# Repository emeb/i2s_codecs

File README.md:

# i2s_codecs

## Abstract
This repository is a collection of hardware and software for evaluating I2S codecs
for use in digital audio projects. I've been using codecs for personal and commercial
applications for more than a decade now and I've seen a lot of them come and go. Recently
several of my go-to codecs went EOL and I had to dive back into the distributors sites to
find a new one to use for some upcoming projects. The first one I tried had some very
odd behavior so I picked a few more, built some breakout boards and a little I2S signal
generator for comparing them all on even footing. The designs here are the result of
that effort.

## Hardware
There are two subdirectories here with KiCAD hardware designs that I used:
* `codec_pmods` - these are simple breakout boards for a number of different codecs,
some of which are currently available, some are obsolete. They are small 2-layer
boards intended to provide minimal support for the codec devices with little to
no attention to audio signal conditioning. The I2S interface is through a standard
12-pin (8 signals + 4 power & ground) PMOD connector that also provides 3 GPIO pins
that support I2C or bitbang configuration protocols that some codecs require for
startup.
* `rp2040_i2s_tester` - this is a KiCAD design for an RP2040 MCU that can drive the
12-pin PMOD with appropriate I2S, I2C or bitbang as well as 3.3V power. It uses a
USB-C connector for power and bootloading but also provides a Qwiic I2C connector,
a blinky LED and a user-defined button for mode selection.

## Software
The directory `Firmware` contains a Raspberry Pi SDK project with basic firmware
for the `rp2040_i2s_tester` board.

## Going Further
This is bare-bones stuff but can support more complex stuff in the future. I may
investigate USB Audio class drivers for interfacing the codecs to a host. There are
also a wide range of other codecs I may add to the list of breakouts. Time will tell.

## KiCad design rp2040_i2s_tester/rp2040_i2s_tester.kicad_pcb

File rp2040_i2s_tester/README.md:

# RP2040_I2S_Tester
I2S Signal Generator for testing CODECs

## Abstract
This directory contains a KiCAD design for an RP2040-based I2S signal generator
that can drive the CODEC PMODs described elsewhere in this repository.

## Firmware
The RP2040 firmware for this design can be found elsewhere in this repository.

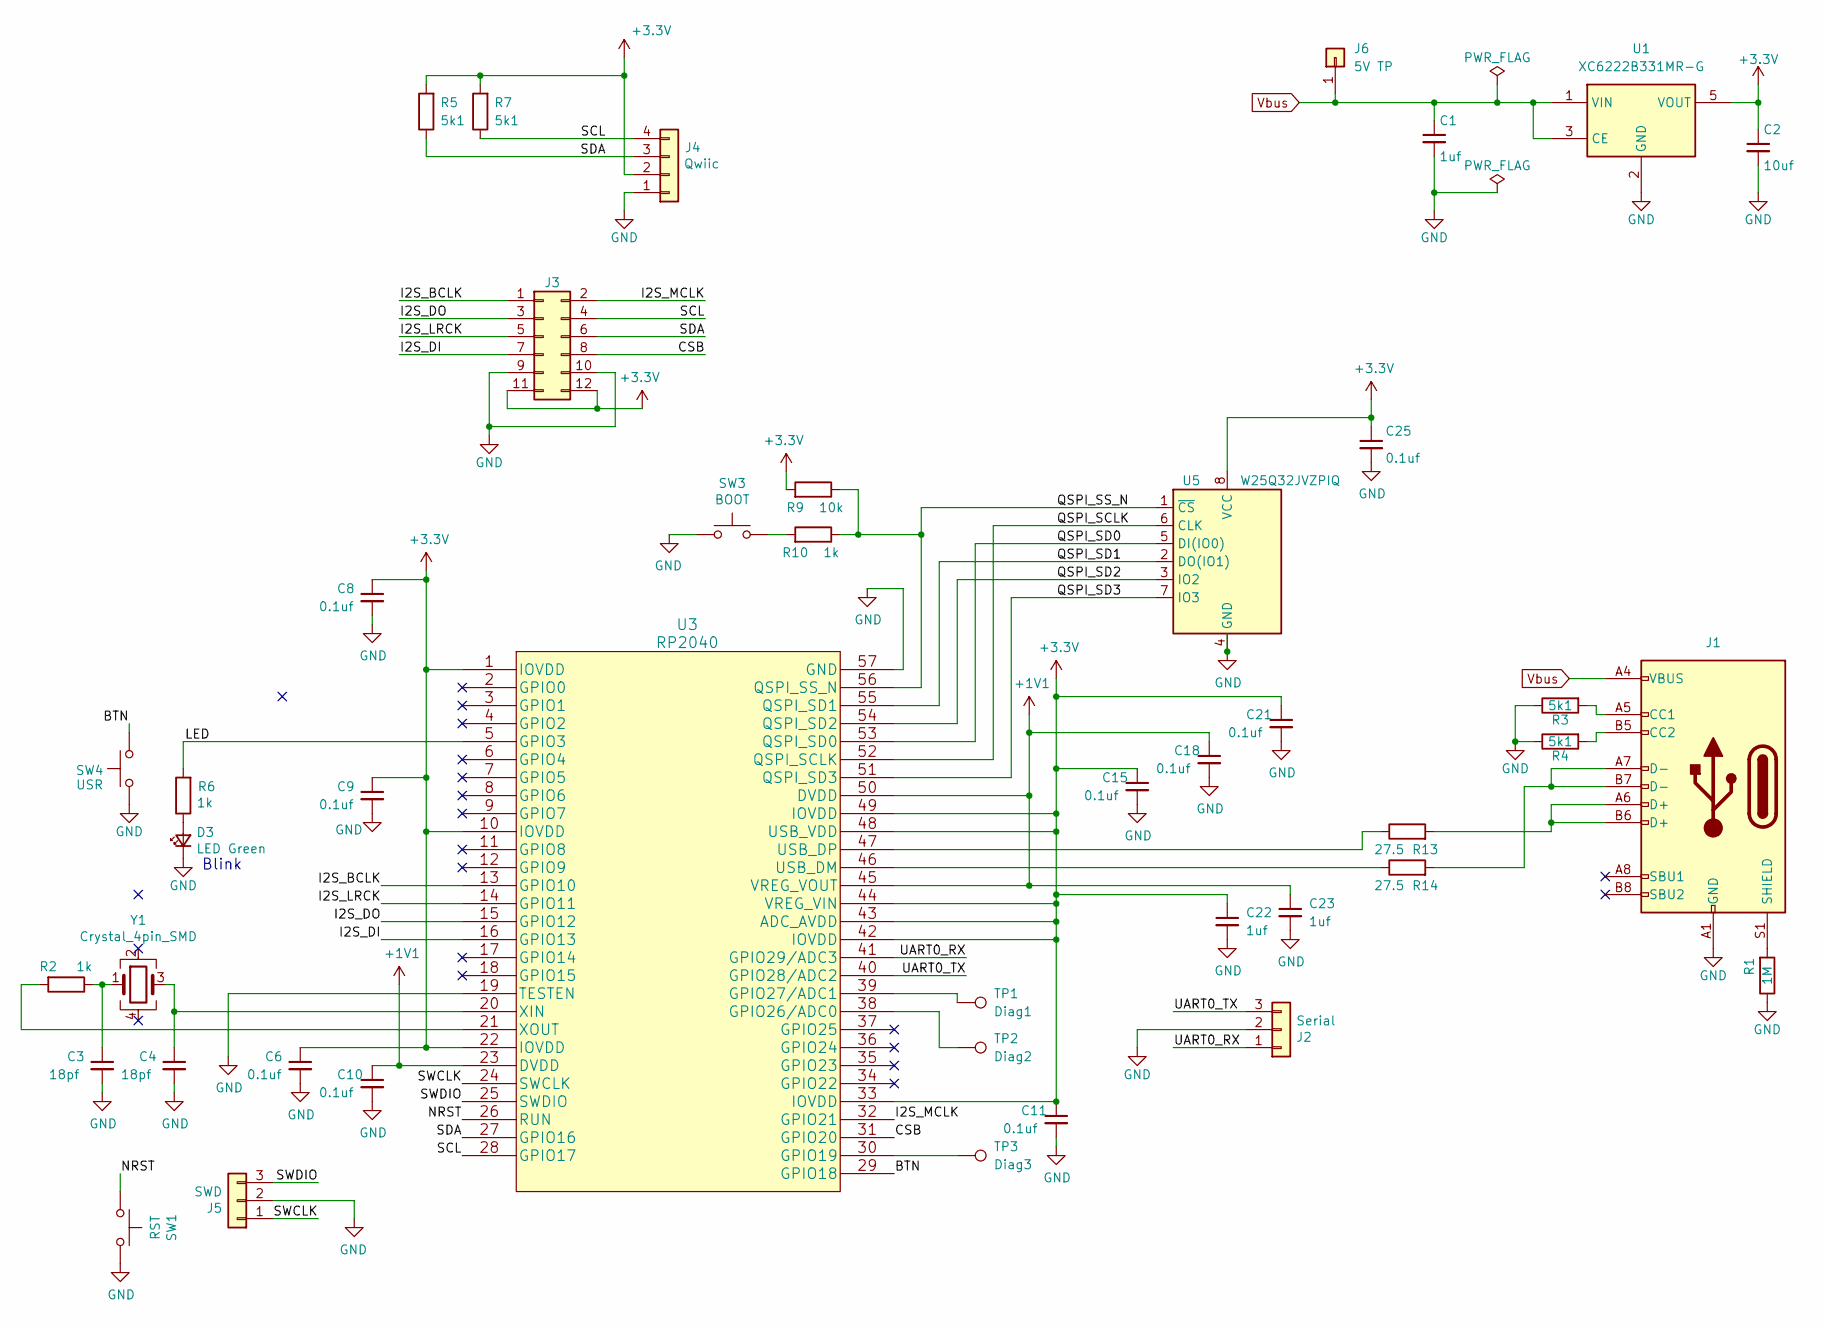
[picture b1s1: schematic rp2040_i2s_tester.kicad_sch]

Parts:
C1, C22, C23: 1uf; C_0402_1005Metric
C2: 10uf; C_0805_2012Metric
C3, C4: 18pf; C_0402_1005Metric
C6, C8, C9, C10, C11, C15, C18, C21, C25: 0.1uf; C_0402_1005Metric
D3: LED Green; LED_0603_1608Metric
J1: USB_C_Receptacle_USB2.0; USB_C_Receptacle_HRO_TYPE-C-31-M-12
J2: Serial; JST_SH_SM03B-SRSS-TB_1x03-1MP_P1.00mm_Horizontal
J3: CONN_02X06; PinSocket_2x06_P2.54mm_Vertical
J4: Qwiic; JST_SH_SM04B-SRSS-TB_04x1.00mm_Angled
J5: SWD; JST_SH_SM03B-SRSS-TB_1x03-1MP_P1.00mm_Horizontal
J6: 5V TP; PinHeader_1x01_P2.54mm_Vertical
R1: 1M; R_0402_1005Metric
R2, R6, R10: 1k; R_0402_1005Metric
R3, R4, R5, R7: 5k1; R_0402_1005Metric
R9: 10k; R_0402_1005Metric
R13, R14: 27.5; R_0402_1005Metric
SW1: RST; SW_Push_1P1T_NO_CK_KMR2
SW3: BOOT; SW_Push_1P1T_NO_CK_KMR2
SW4: USR; SW_Push_1P1T_NO_CK_KMR2
TP1: Diag1; TestPoint_Pad_D1.0mm
TP2: Diag2; TestPoint_Pad_D1.0mm
TP3: Diag3; TestPoint_Pad_D1.0mm
U1: XC6222B331MR-G; SOT-23-5
U3: RP2040
U5: W25Q32JVZPIQ; WSON-8-1EP_6x5mm_P1.27mm_EP3.4x4.3mm
Y1: Crystal_4pin_SMD; Crystal_SMD_3225-4Pin_3.2x2.5mm

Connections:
+1V1: C10.1, C18.1, C23.1, U3.23 (DVDD), U3.45 (VREG_VOUT), U3.50 (DVDD)
+3.3V: C2.1, C6.1, C8.1, C9.1, C11.1, C15.1, C21.1, C22.1, C25.1, J3.11, J3.12, J4.2, R5.2, R7.2, R9.2, U1.5 (VOUT), U3.1 (IOVDD), U3.10 (IOVDD), U3.22 (IOVDD), U3.33 (IOVDD), U3.42 (IOVDD), U3.43 (ADC_AVDD), U3.44 (VREG_VIN), U3.48 (USB_VDD), U3.49 (IOVDD), U5.8 (VCC)
/BTN: SW4.2, U3.29 (GPIO18)
/CSB: J3.8, U3.31 (GPIO20)
/I2S_BCLK: J3.1, U3.13 (GPIO10)
/I2S_DI: J3.7, U3.16 (GPIO13)
/I2S_DO: J3.3, U3.15 (GPIO12)
/I2S_LRCK: J3.5, U3.14 (GPIO11)
/I2S_MCLK: J3.2, U3.32 (GPIO21)
/LED: R6.2, U3.5 (GPIO3)
/NRST: SW1.1, U3.26 (RUN)
/QSPI_SCLK: U3.52 (QSPI_SCLK), U5.6 (CLK)
/QSPI_SD0: U3.53 (QSPI_SD0), U5.5 (DI(IO0))
/QSPI_SD1: U3.55 (QSPI_SD1), U5.2 (DO(IO1))
/QSPI_SD2: U3.54 (QSPI_SD2), U5.3 (IO2)
/QSPI_SD3: U3.51 (QSPI_SD3), U5.7 (IO3)
/QSPI_SS_N: R9.1, R10.1, U3.56 (QSPI_SS_N), U5.1 (~CS)
/SCL: J3.4, J4.4, R7.1, U3.28 (GPIO17)
/SDA: J3.6, J4.3, R5.1, U3.27 (GPIO16)
/SWCLK: J5.1, U3.24 (SWCLK)
/SWDIO: J5.3, U3.25 (SWDIO)
/UART0_RX: J2.1, U3.41 (GPIO29/ADC3)
/UART0_TX: J2.3, U3.40 (GPIO28/ADC2)
GND: C1.2, C2.2, C3.2, C4.2, C6.2, C8.2, C9.2, C10.2, C11.2, C15.2, C18.2, C21.2, C22.2, C23.2, C25.2, D3.1 (K), J1.A1 (GND), J1.A12 (GND), J1.B1 (GND), J1.B12 (GND), J2.2, J3.9, J3.10, J4.1, J5.2, R1.1, R3.1, R4.1, SW1.2, SW3.2, SW4.1, U1.2 (GND), U3.19 (TESTEN), U3.57 (GND), U5.4 (GND)
unnamed: C3.1, R2.1, Y1.1
unnamed: D3.2 (A), R6.1
unnamed: J1.A5 (CC1), R3.2
unnamed: J1.B5 (CC2), R4.2
unnamed: J1.A6 (D+), J1.B6 (D+), R13.2
unnamed: J1.A7 (D-), J1.B7 (D-), R14.2
unnamed: J1.S1 (SHIELD), R1.2
unnamed: R10.2, SW3.1
unnamed: TP3.1, U3.30 (GPIO19)
unnamed: TP2.1, U3.38 (GPIO26/ADC0)
unnamed: TP1.1, U3.39 (GPIO27/ADC1)
unnamed: R14.1, U3.46 (USB_DM)
unnamed: R13.1, U3.47 (USB_DP)
unnamed: C4.1, U3.20 (XIN), Y1.3
unnamed: R2.2, U3.21 (XOUT)
Vbus: C1.1, J1.A4 (VBUS), J1.A9 (VBUS), J1.B4 (VBUS), J1.B9 (VBUS), J6.1, U1.1 (VIN), U1.3 (CE)

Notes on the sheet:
Blink

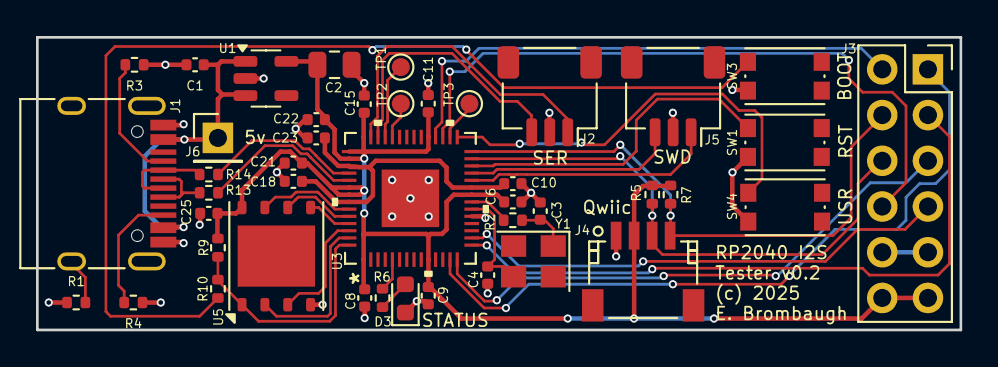
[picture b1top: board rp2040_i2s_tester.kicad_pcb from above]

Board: 2 copper layers, 51.3 x 16.3 mm, 43 parts (0 on the bottom side), 40 nets.

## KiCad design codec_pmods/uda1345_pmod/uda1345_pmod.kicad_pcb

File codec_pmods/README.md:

# CODEC PMODS
This directory contains KiCAD designs for various CODEC PMOD breakout boards. The
following boards have been built and tested:
* WM8731 - this is an earlier design found in an [older repository](https://github.com/emeb/Old_Website/tree/main/synth/codec_pmod).
It's a venerable codec that's been used in a lot of computers and media players as well as
add-on boards for the Raspberry Pi but now it's obsolete.
* TLV320AIC3101 - this is a currently available (as of 2025) codec that has some interesting
peculiarities that may make it unsuitable for some applications.
* NAU88C22 - this is an inexpensive codec with a lot of interesting features that seems to
perform reasonably well.
* SGTL5000 - this one has been around for a while and is still available. It's notable for its
small size.
* UDA1345 - This is a long obsolete part that I included just because I had a few in my
parts inventory that I'd never tried out. It's idiosyncratic.

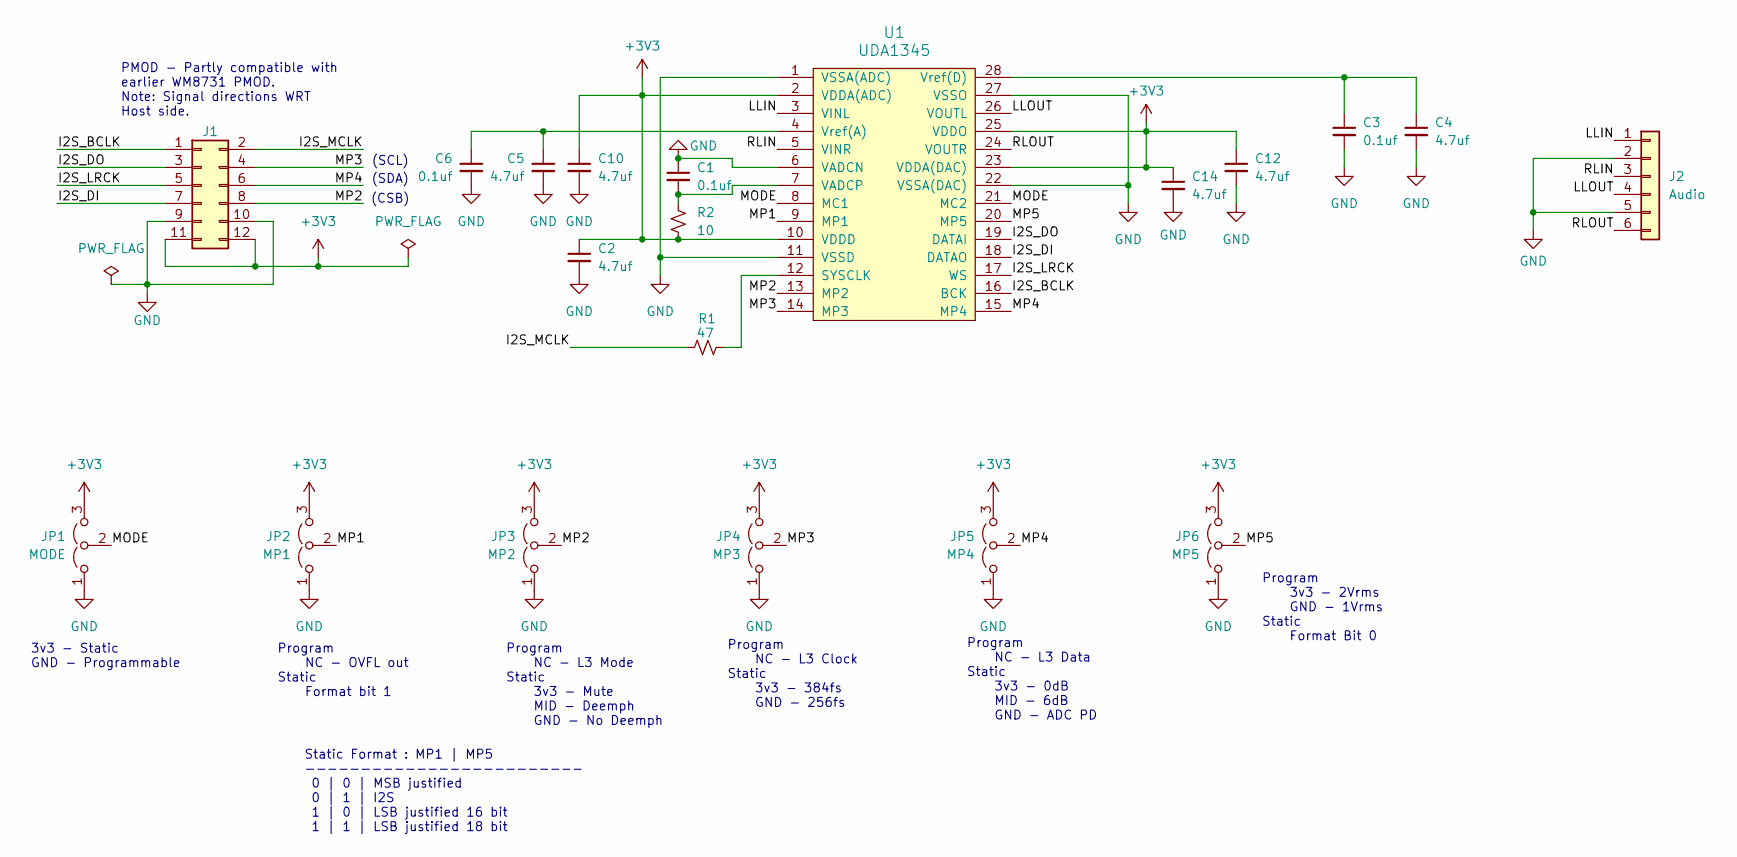
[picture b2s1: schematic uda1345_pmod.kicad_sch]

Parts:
C1, C3, C6: 0.1uf; C_0402_1005Metric
C2, C4, C5, C10, C12, C14: 4.7uf; C_0402_1005Metric
J1: CONN_02X06; PinHeader_2x06_P2.54mm_Vertical
J2: Audio; PinHeader_1x06_P2.54mm_Vertical
JP1: MODE; SolderJumper-3_P1.3mm_Open_RoundedPad1.0x1.5mm
JP2: MP1; SolderJumper-3_P1.3mm_Open_RoundedPad1.0x1.5mm
JP3: MP2; SolderJumper-3_P1.3mm_Open_RoundedPad1.0x1.5mm
JP4: MP3; SolderJumper-3_P1.3mm_Open_RoundedPad1.0x1.5mm
JP5: MP4; SolderJumper-3_P1.3mm_Open_RoundedPad1.0x1.5mm
JP6: MP5; SolderJumper-3_P1.3mm_Open_RoundedPad1.0x1.5mm
R1: 47; R_0603_1608Metric
R2: 10; R_0603_1608Metric
U1: UDA1345; SSOP-28_5.3x10.2mm_P0.65mm

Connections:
+3V3: C2.1, C10.1, C12.1, C14.1, J1.11, J1.12, JP1.3 (B), JP2.3 (B), JP3.3 (B), JP4.3 (B), JP5.3 (B), JP6.3 (B), R2.1, U1.2 (VDDA(ADC)), U1.10 (VDDD), U1.23 (VDDA(DAC)), U1.25 (VDDO)
/I2S_BCLK: J1.1, U1.16 (BCK)
/I2S_DI: J1.7, U1.18 (DATAO)
/I2S_DO: J1.3, U1.19 (DATAI)
/I2S_LRCK: J1.5, U1.17 (WS)
/I2S_MCLK: J1.2, R1.2
/LLIN: J2.1, U1.3 (VINL)
/LLOUT: J2.4, U1.26 (VOUTL)
/MODE: JP1.2 (C), U1.8 (MC1), U1.21 (MC2)
/MP1: JP2.2 (C), U1.9 (MP1)
/MP2: J1.8, JP3.2 (C), U1.13 (MP2)
/MP3: J1.4, JP4.2 (C), U1.14 (MP3)
/MP4: J1.6, JP5.2 (C), U1.15 (MP4)
/MP5: JP6.2 (C), U1.20 (MP5)
/RLIN: J2.3, U1.5 (VINR)
/RLOUT: J2.6, U1.24 (VOUTR)
GND: C1.1, C2.2, C3.2, C4.2, C5.2, C6.2, C10.2, C12.2, C14.2, J1.9, J1.10, J2.2, J2.5, JP1.1 (A), JP2.1 (A), JP3.1 (A), JP4.1 (A), JP5.1 (A), JP6.1 (A), U1.1 (VSSA(ADC)), U1.6 (VADCN), U1.11 (VSSD), U1.22 (VSSA(DAC)), U1.27 (VSSO)
unnamed: R1.1, U1.12 (SYSCLK)
unnamed: C1.2, R2.2, U1.7 (VADCP)
unnamed: C5.1, C6.1, U1.4 (Vref(A))
unnamed: C3.1, C4.1, U1.28 (Vref(D))

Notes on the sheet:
Program NC - OVFL out Static Format bit 1
Program 3v3 - 2Vrms GND - 1Vrms Static Format Bit 0
Program NC - L3 Mode Static 3v3 - Mute MID - Deemph GND - No Deemph
3v3 - Static GND - Programmable
Static Format : MP1 | MP5 ------------------------- 0 | 0 | MSB justified 0 | 1 | I2S 1 | 0 | LSB justified 16 bit 1 | 1 | LSB justified 18 bit
(SCL)
(SDA)
Program NC - L3 Clock Static 3v3 - 384fs GND - 256fs
Program NC - L3 Data Static 3v3 - 0dB MID - 6dB GND - ADC PD
PMOD - Partly compatible with earlier WM8731 PMOD. Note: Signal directions WRT Host side.
(CSB)

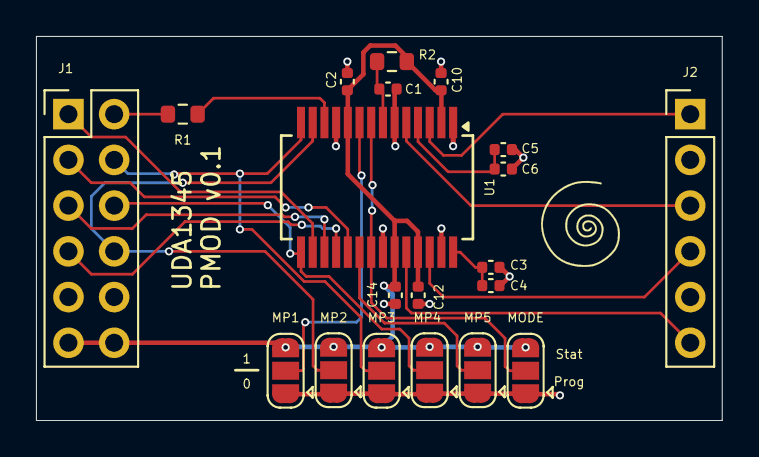
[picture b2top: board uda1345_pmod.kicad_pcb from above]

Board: 2 copper layers, 38.1 x 21.3 mm, 21 parts (0 on the bottom side), 21 nets.

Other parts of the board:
Ref**: Val**; avatar_small

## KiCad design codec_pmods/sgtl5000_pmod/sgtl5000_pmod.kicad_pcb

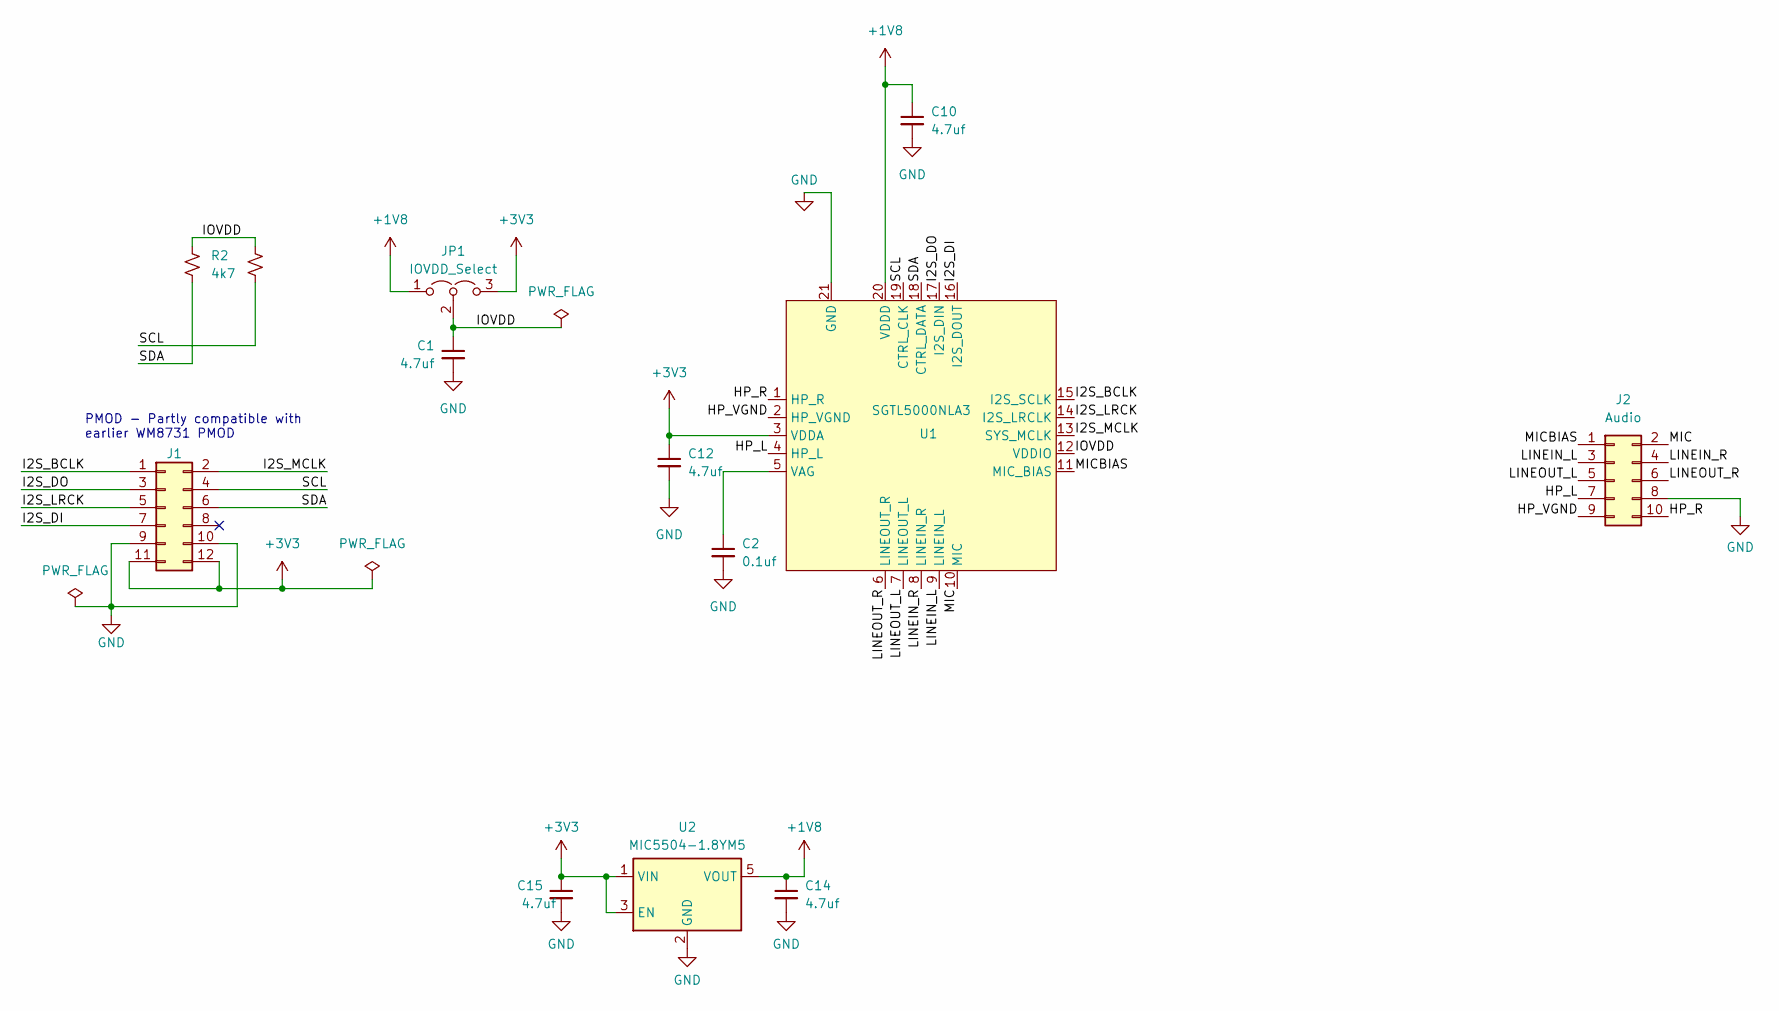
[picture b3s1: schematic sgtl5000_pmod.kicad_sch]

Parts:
C1, C10, C12, C14, C15: 4.7uf; C_0402_1005Metric
C2: 0.1uf; C_0402_1005Metric
J1: CONN_02X06; PinHeader_2x06_P2.54mm_Vertical
J2: Audio; PinHeader_2x05_P2.54mm_Vertical
JP1: IOVDD_Select; SolderJumper-3_P1.3mm_Open_RoundedPad1.0x1.5mm
R2, R3: 4k7; R_0603_1608Metric
U1: SGTL5000NLA3; QFN-20-1EP_3x3mm_P0.4mm_EP1.65x1.65mm_ThermalVias
U2: MIC5504-1.8YM5; SOT-23-5

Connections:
+1V8: C10.1, C14.1, JP1.1 (A), U1.20 (VDDD), U2.5 (VOUT)
+3V3: C12.1, C15.1, J1.11, J1.12, JP1.3 (B), U1.3 (VDDA), U2.1 (VIN), U2.3 (EN)
/HP_L: J2.7, U1.4 (HP_L)
/HP_R: J2.10, U1.1 (HP_R)
/HP_VGND: J2.9, U1.2 (HP_VGND)
/I2S_BCLK: J1.1, U1.15 (I2S_SCLK)
/I2S_DI: J1.7, U1.16 (I2S_DOUT)
/I2S_DO: J1.3, U1.17 (I2S_DIN)
/I2S_LRCK: J1.5, U1.14 (I2S_LRCLK)
/I2S_MCLK: J1.2, U1.13 (SYS_MCLK)
/IOVDD: C1.1, JP1.2 (C), R2.2, R3.2, U1.12 (VDDIO)
/LINEIN_L: J2.3, U1.9 (LINEIN_L)
/LINEIN_R: J2.4, U1.8 (LINEIN_R)
/LINEOUT_L: J2.5, U1.7 (LINEOUT_L)
/LINEOUT_R: J2.6, U1.6 (LINEOUT_R)
/MIC: J2.2, U1.10 (MIC)
/MICBIAS: J2.1, U1.11 (MIC_BIAS)
/SCL: J1.4, R3.1, U1.19 (CTRL_CLK)
/SDA: J1.6, R2.1, U1.18 (CTRL_DATA)
GND: C1.2, C2.2, C10.2, C12.2, C14.2, C15.2, J1.9, J1.10, J2.8, U1.21 (GND), U2.2 (GND)
unnamed: C2.1, U1.5 (VAG)

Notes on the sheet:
PMOD - Partly compatible with earlier WM8731 PMOD

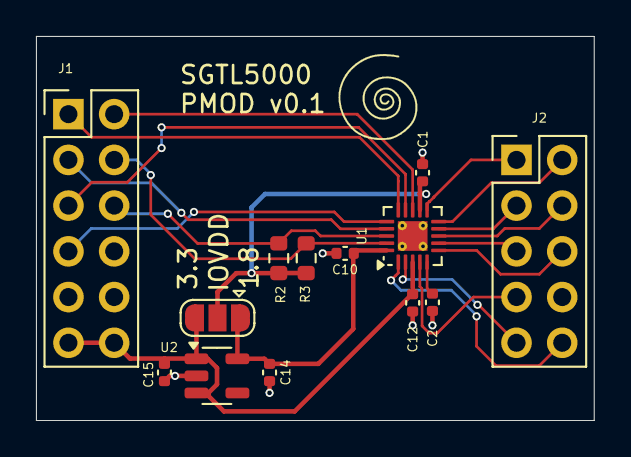
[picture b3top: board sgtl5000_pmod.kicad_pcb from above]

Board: 2 copper layers, 31.0 x 21.3 mm, 14 parts (0 on the bottom side), 21 nets.

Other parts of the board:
Ref**: Val**; avatar_small

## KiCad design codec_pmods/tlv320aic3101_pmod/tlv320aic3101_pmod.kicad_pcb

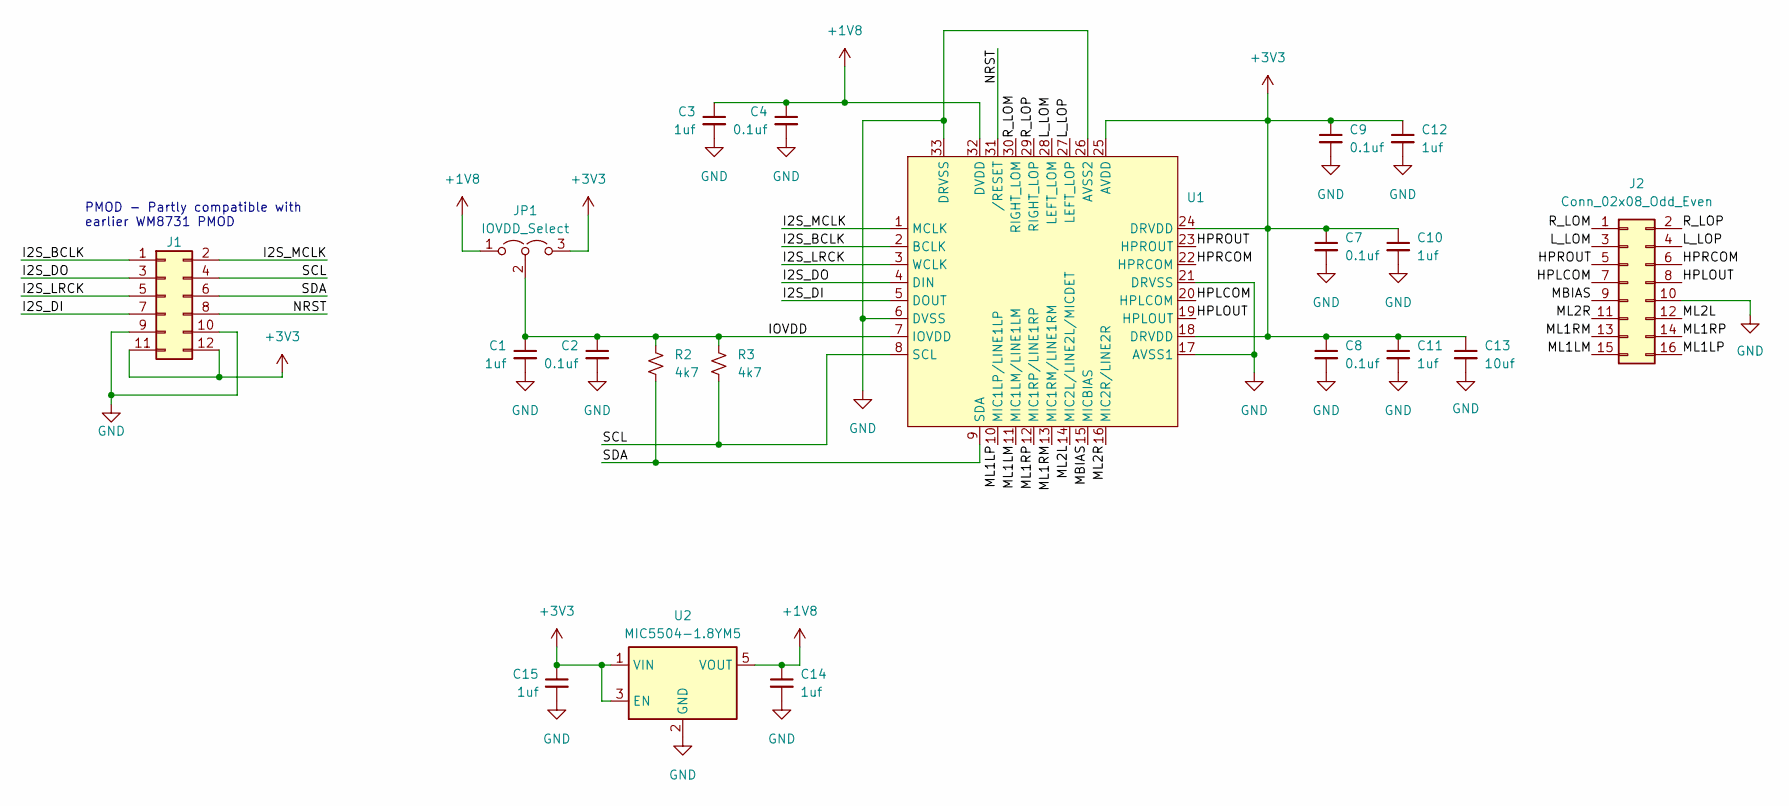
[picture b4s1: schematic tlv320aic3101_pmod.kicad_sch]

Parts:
C1, C3, C10, C11, C12, C14, C15: 1uf; C_0603_1608Metric
C2, C4, C7, C8, C9: 0.1uf; C_0603_1608Metric
C13: 10uf; C_0805_2012Metric
J1: CONN_02X06; PinHeader_2x06_P2.54mm_Vertical
J2: Conn_02x08_Odd_Even; PinHeader_2x08_P2.54mm_Vertical
JP1: IOVDD_Select; SolderJumper-3_P1.3mm_Open_RoundedPad1.0x1.5mm
R2, R3: 4k7; R_0603_1608Metric
U1: QFN-32-1EP_5x5mm_P0.5mm_EP3.6x3.6mm
U2: MIC5504-1.8YM5; SOT-23-5

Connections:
+1V8: C3.1, C4.1, C14.1, JP1.1 (A), U1.32 (DVDD), U2.5 (VOUT)
+3V3: C7.1, C8.1, C9.1, C10.1, C11.1, C12.1, C13.1, C15.1, J1.11, J1.12, JP1.3 (B), U1.18 (DRVDD), U1.24 (DRVDD), U1.25 (AVDD), U2.1 (VIN), U2.3 (EN)
/HPLCOM: J2.7, U1.20 (HPLCOM)
/HPLOUT: J2.8, U1.19 (HPLOUT)
/HPRCOM: J2.6, U1.22 (HPRCOM)
/HPROUT: J2.5, U1.23 (HPROUT)
/I2S_BCLK: J1.1, U1.2 (BCLK)
/I2S_DI: J1.7, U1.5 (DOUT)
/I2S_DO: J1.3, U1.4 (DIN)
/I2S_LRCK: J1.5, U1.3 (WCLK)
/I2S_MCLK: J1.2, U1.1 (MCLK)
/IOVDD: C1.1, C2.1, JP1.2 (C), R2.2, R3.2, U1.7 (IOVDD)
/L_LOM: J2.3, U1.28 (LEFT_LOM)
/L_LOP: J2.4, U1.27 (LEFT_LOP)
/MBIAS: J2.9, U1.15 (MICBIAS)
/ML1LM: J2.15, U1.11 (MIC1LM/LINE1LM)
/ML1LP: J2.16, U1.10 (MIC1LP/LINE1LP)
/ML1RM: J2.13, U1.13 (MIC1RM/LINE1RM)
/ML1RP: J2.14, U1.12 (MIC1RP/LINE1RP)
/ML2L: J2.12, U1.14 (MIC2L/LINE2L/MICDET)
/ML2R: J2.11, U1.16 (MIC2R/LINE2R)
/NRST: J1.8, U1.31 (/RESET)
/R_LOM: J2.1, U1.30 (RIGHT_LOM)
/R_LOP: J2.2, U1.29 (RIGHT_LOP)
/SCL: J1.4, R3.1, U1.8 (SCL)
/SDA: J1.6, R2.1, U1.9 (SDA)
GND: C1.2, C2.2, C3.2, C4.2, C7.2, C8.2, C9.2, C10.2, C11.2, C12.2, C13.2, C14.2, C15.2, J1.9, J1.10, J2.10, U1.6 (DVSS), U1.17 (AVSS1), U1.21 (DRVSS), U1.26 (AVSS2), U1.33 (DRVSS), U2.2 (GND)

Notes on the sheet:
PMOD - Partly compatible with earlier WM8731 PMOD

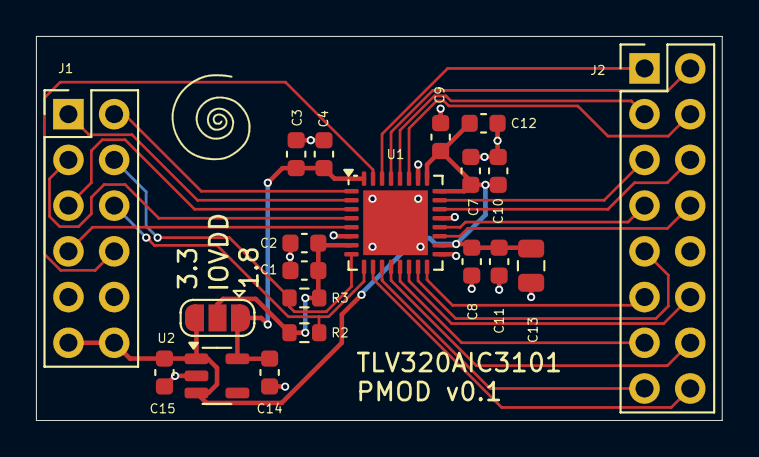
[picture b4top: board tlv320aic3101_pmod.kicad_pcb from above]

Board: 2 copper layers, 38.1 x 21.3 mm, 22 parts (1 on the bottom side), 27 nets.

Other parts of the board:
Ref**: Val**; avatar_small
Ref**#2: Val**; avatar_small

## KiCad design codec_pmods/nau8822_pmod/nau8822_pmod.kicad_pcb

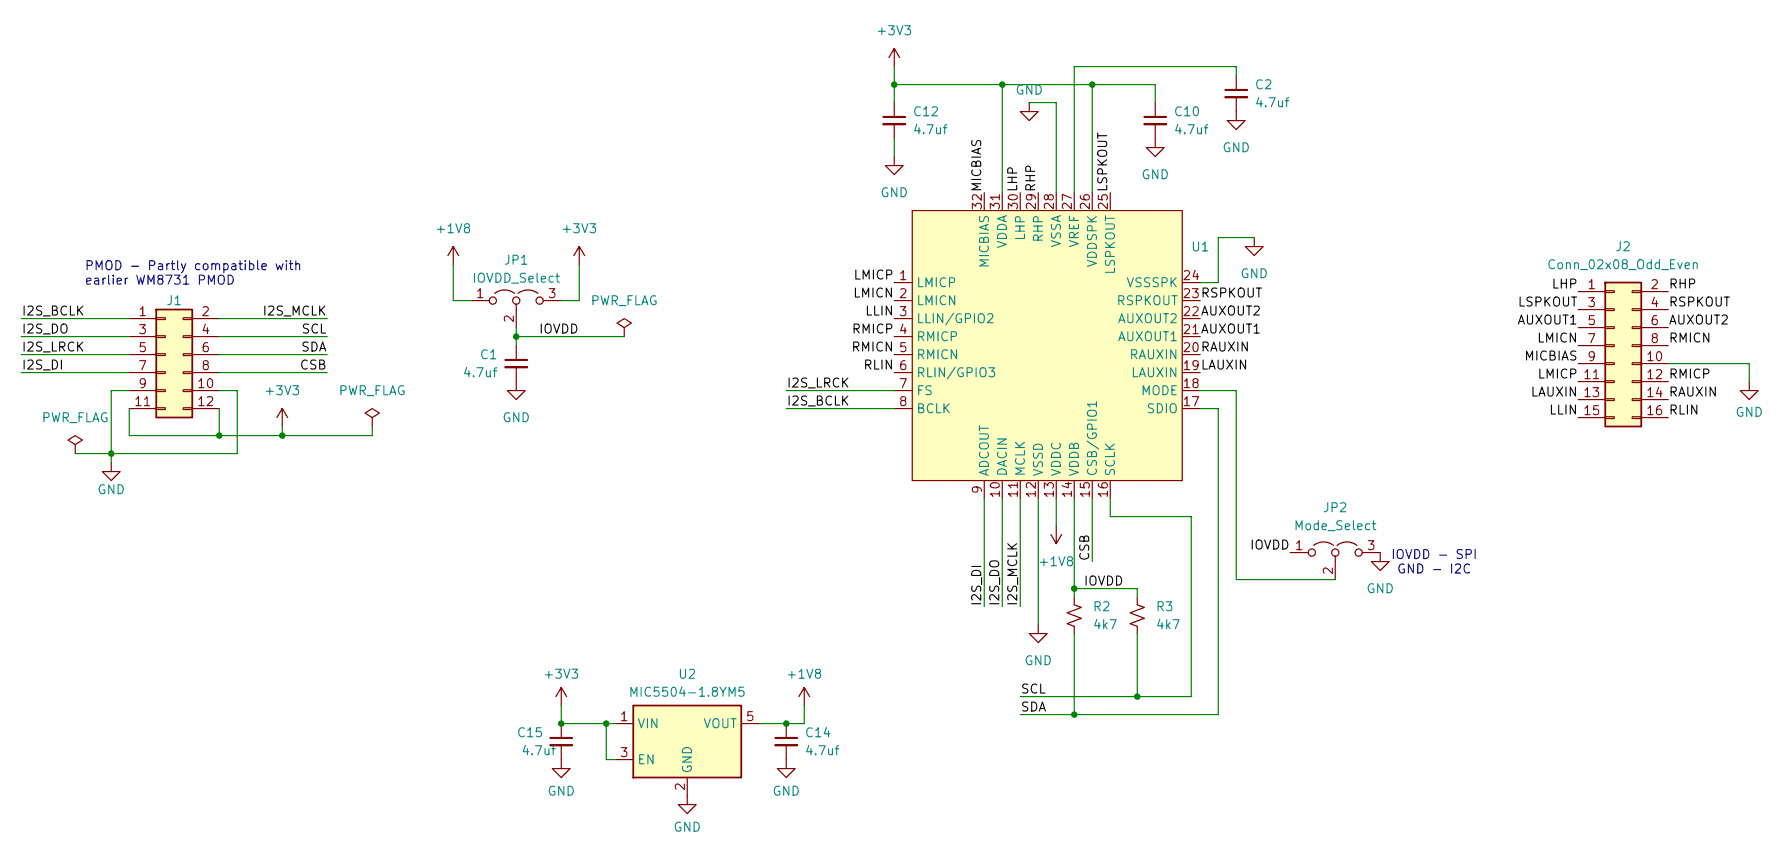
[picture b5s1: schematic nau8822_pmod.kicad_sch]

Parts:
C1, C2, C10, C12, C14, C15: 4.7uf; C_0402_1005Metric
J1: CONN_02X06; PinHeader_2x06_P2.54mm_Vertical
J2: Conn_02x08_Odd_Even; PinHeader_2x08_P2.54mm_Vertical
JP1: IOVDD_Select; SolderJumper-3_P1.3mm_Open_RoundedPad1.0x1.5mm
JP2: Mode_Select; SolderJumper-3_P1.3mm_Open_RoundedPad1.0x1.5mm
R2, R3: 4k7; R_0603_1608Metric
U1: QFN-32-1EP_5x5mm_P0.5mm_EP3.1x3.1mm
U2: MIC5504-1.8YM5; SOT-23-5

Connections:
+1V8: C14.1, JP1.1 (A), U1.13 (VDDC), U2.5 (VOUT)
+3V3: C10.1, C12.1, C15.1, J1.11, J1.12, JP1.3 (B), U1.26 (VDDSPK), U1.31 (VDDA), U2.1 (VIN), U2.3 (EN)
/AUXOUT1: J2.5, U1.21 (AUXOUT1)
/AUXOUT2: J2.6, U1.22 (AUXOUT2)
/CSB: J1.8, U1.15 (CSB/GPIO1)
/I2S_BCLK: J1.1, U1.8 (BCLK)
/I2S_DI: J1.7, U1.9 (ADCOUT)
/I2S_DO: J1.3, U1.10 (DACIN)
/I2S_LRCK: J1.5, U1.7 (FS)
/I2S_MCLK: J1.2, U1.11 (MCLK)
/IOVDD: C1.1, JP1.2 (C), JP2.1 (A), R2.2, R3.2, U1.14 (VDDB)
/LAUXIN: J2.13, U1.19 (LAUXIN)
/LHP: J2.1, U1.30 (LHP)
/LLIN: J2.15, U1.3 (LLIN/GPIO2)
/LMICN: J2.7, U1.2 (LMICN)
/LMICP: J2.11, U1.1 (LMICP)
/LSPKOUT: J2.3, U1.25 (LSPKOUT)
/MICBIAS: J2.9, U1.32 (MICBIAS)
/RAUXIN: J2.14, U1.20 (RAUXIN)
/RHP: J2.2, U1.29 (RHP)
/RLIN: J2.16, U1.6 (RLIN/GPIO3)
/RMICN: J2.8, U1.5 (RMICN)
/RMICP: J2.12, U1.4 (RMICP)
/RSPKOUT: J2.4, U1.23 (RSPKOUT)
/SCL: J1.4, R3.1, U1.16 (SCLK)
/SDA: J1.6, R2.1, U1.17 (SDIO)
GND: C1.2, C2.2, C10.2, C12.2, C14.2, C15.2, J1.9, J1.10, J2.10, JP2.3 (B), U1.12 (VSSD), U1.24 (VSSSPK), U1.28 (VSSA), U2.2 (GND)
unnamed: JP2.2 (C), U1.18 (MODE)
unnamed: C2.1, U1.27 (VREF)

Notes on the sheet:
IOVDD - SPI GND - I2C
PMOD - Partly compatible with earlier WM8731 PMOD

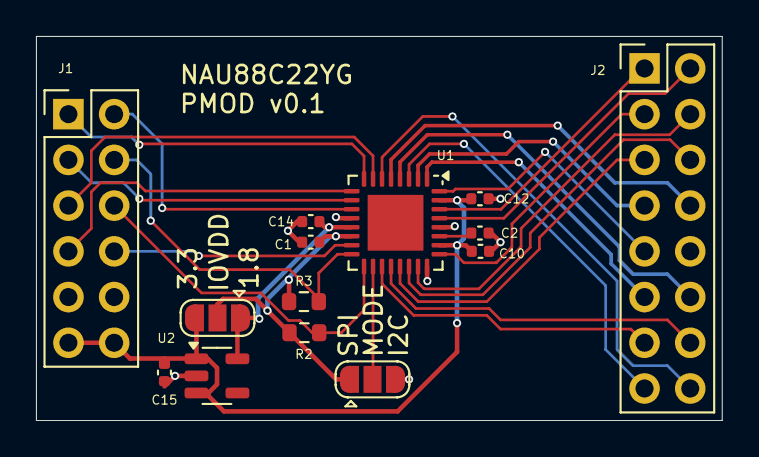
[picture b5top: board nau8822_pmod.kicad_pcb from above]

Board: 2 copper layers, 38.1 x 21.3 mm, 14 parts (0 on the bottom side), 29 nets.

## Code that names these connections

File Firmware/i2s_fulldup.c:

/*
 * i2s_fulldup.c - PIO-based full-duplex I2S for RP2040
 * 12-19-21 E. Brombaugh
 *
 * Based on original ideas from
 * https://gist.github.com/jonbro/3da573315f066be8ea390db39256f9a7
 * and the pico-extras library.
 */

#include <stdio.h>
#include <string.h>
#include "i2s_fulldup.h"
#include "hardware/dma.h"
#include "hardware/irq.h"
#include "hardware/pio.h"
#include "hardware/structs/clocks.h"
#include "hardware/clocks.h"
#include "pico/multicore.h"
#include "i2s_fulldup.pio.h"
#include "audio.h"

/* uncomment this to run audio processing on core 1 */
#define MULTICORE

/* uncomment this if using old Pico SDK */
//#define OLD_SDK

/* I2S PIO has L+R (Frames) in 32-bits */
#define FRAMES_PER_BUFFER (BUFSZ/2)

/* I2S comes out on these pins */
#define I2S_DO_PIN 12		// data out
#define I2S_DI_PIN 13		// data in
#define I2S_CLK_PIN_BASE 10	// BCLK, LRCK
#define I2S_MCLK_PIN 21		// MCLK

#define IN_DIAG_PIN 26
#define OUT_DIAG_PIN 27

/* resources we use */
PIO pio;
uint sm;
uint dma_chan_input, dma_chan_output;
uint ib_idx, ob_idx;
uint32_t input_buf[2*FRAMES_PER_BUFFER], output_buf[2*FRAMES_PER_BUFFER],
	xfer_buf[FRAMES_PER_BUFFER];
uint32_t Fsample;

/*
 * IRQ0 handler - used only for I2S input
 * ATM this is not double-buffered, but it would be prudent to
 * do so if adding code to compute the next buffer.
 */
void dma_input_handler(void)
{
	gpio_put(IN_DIAG_PIN, 1);
	
	/* Clear IRQ for I2S input */
	dma_channel_acknowledge_irq0(dma_chan_input);
	
	/* reset write address to start of next buffer */
	ib_idx ^= 1;
	dma_channel_set_write_addr(dma_chan_input,
		&input_buf[ib_idx*FRAMES_PER_BUFFER],
		true
	);
	
	/* start next transfer sequence */
	dma_channel_start(dma_chan_input);
	
	/* process to transfer buffer */
	Audio_Proc((int16_t *)xfer_buf,
	(int16_t *)&input_buf[(ib_idx^1)*FRAMES_PER_BUFFER],
		2*FRAMES_PER_BUFFER);

	gpio_put(IN_DIAG_PIN, 0);
}

/*
 * IRQ1 handler - used only for I2S output
 * ATM this is not double-buffered, but it would be prudent to
 * do so if adding code to compute the next buffer.
 */
void dma_output_handler()
{
	gpio_put(OUT_DIAG_PIN, 1);
	
	/* Clear IRQ for I2S output */
    dma_channel_acknowledge_irq1(dma_chan_output);
	
	/* reset read address to start of next buffer */
	ob_idx ^= 1;
	dma_channel_set_read_addr(dma_chan_output,
		&output_buf[ob_idx*FRAMES_PER_BUFFER],
		true
	);
	
	/* start next transfer sequence */
	dma_channel_start(dma_chan_output);
	
	/* copy from transfer buffer */
	memcpy(&output_buf[ob_idx*FRAMES_PER_BUFFER], xfer_buf,
		FRAMES_PER_BUFFER*sizeof(uint32_t));

	gpio_put(OUT_DIAG_PIN, 0);
}

#ifdef MULTICORE
/*
 * entry point for 2nd core to start running
 */
void core1_entry()
{
	/* enable IRQ handler for dma input */
    irq_set_exclusive_handler(DMA_IRQ_0, dma_input_handler);
    irq_set_enabled(DMA_IRQ_0, true);
	

	/* enable IRQ handler for dma output */
    irq_set_exclusive_handler(DMA_IRQ_1, dma_output_handler);
    irq_set_enabled(DMA_IRQ_1, true);
	
	/* enable multicore lockout */
	multicore_lockout_victim_init();

	/* loop here waiting for IRQs */
	while(1)
	{
		Audio_Fore();
	}
}
#endif

/*
 * initialize the I2S processing
 */
void init_i2s_fulldup(void)
{
	int32_t i;
	int16_t *obuf = (int16_t *)output_buf;
	int16_t *ibuf = (int16_t *)input_buf;
	
	/* clear buffers */
	for(i=0;i<2*FRAMES_PER_BUFFER;i++)
	{
		*ibuf++ = 0;
		*ibuf++ = 0;
		*obuf++ = i<<10;
		*obuf++ = i<<10;
	}
	ib_idx = ob_idx = 0;
	
	/* diag GPIO */
	gpio_init(IN_DIAG_PIN);
	gpio_set_dir(IN_DIAG_PIN, GPIO_OUT);
	gpio_init(OUT_DIAG_PIN);
	gpio_set_dir(OUT_DIAG_PIN, GPIO_OUT);

    /* set up PIO */
    pio = pio0;
    uint offset = pio_add_program(pio, &i2s_fulldup_program);
    printf("loaded program at offset: %i\n", offset);
    sm = pio_claim_unused_sm(pio, true);
    printf("claimed sm: %i\n", sm);
	
	/* compute PIO divider for desired sample rate */
    uint32_t system_clock_frequency = clock_get_hz(clk_sys);
    assert(system_clock_frequency < 0x40000000);
    printf("System clock %u Hz\n", (uint) system_clock_frequency);
    uint32_t sample_freq = 48000;
    printf("Target sample freq %d\n", sample_freq);
    uint32_t divider = system_clock_frequency * 2 / sample_freq; // avoid arithmetic overflow
    divider = divider & ~(0x1ff); // mask off bottom 9 for exact MCLK/BCLK ratio of 4.0
    assert(divider < 0x1000000);
    printf("PIO clock divider 0x%x/256\n", divider);
	Fsample = 2 * system_clock_frequency / divider;
	printf("Actual sample freq = %d\n", Fsample);
	
	/* set up the PIO and divider */
    i2s_fulldup_program_init(
		pio,
		sm,
		offset,
		I2S_DO_PIN,
		I2S_DI_PIN,
		I2S_CLK_PIN_BASE
	);
    pio_sm_set_clkdiv_int_frac(pio, sm, divider >> 8u, divider & 0xffu);
	
	/* generate an MCLK on GPIO at 8x BCLK (256x LRCK) */
	gpio_set_function(I2S_MCLK_PIN, GPIO_FUNC_GPCK);
	clock_gpio_init(I2S_MCLK_PIN, CLOCKS_CLK_GPOUT1_CTRL_AUXSRC_VALUE_CLK_SYS, divider>>9);
	printf("MCLK at %d Hz\n", system_clock_frequency/(divider>>9));
	
    /* configure dma channel for input */
	ib_idx = 0;
    dma_chan_input = dma_claim_unused_channel(true);
	printf("DMA input using chl %d\n", dma_chan_input);
    dma_channel_config c = dma_channel_get_default_config(dma_chan_input);
    channel_config_set_read_increment(&c,false);
    channel_config_set_write_increment(&c,true);
    channel_config_set_dreq(&c,pio_get_dreq(pio,sm,false));
    channel_config_set_transfer_data_size(&c, DMA_SIZE_32);

    dma_channel_configure(
        dma_chan_input,
        &c,
        input_buf, 			// Destination pointer
        &pio->rxf[sm], 		// Source pointer
        FRAMES_PER_BUFFER, // Number of transfers
        true				// Start immediately
    );
    dma_channel_set_irq0_enabled(dma_chan_input, true);

    /* configure dma channel for output */
	ob_idx = 0;
	dma_chan_output = dma_claim_unused_channel(true);
	printf("DMA output using chl %d\n", dma_chan_output);
    dma_channel_config cc = dma_channel_get_default_config(dma_chan_output);
    channel_config_set_read_increment(&cc,true);
    channel_config_set_write_increment(&cc,false);
    channel_config_set_dreq(&cc,pio_get_dreq(pio,sm,true));
    channel_config_set_transfer_data_size(&cc, DMA_SIZE_32);
    dma_channel_configure(
        dma_chan_output,
        &cc,
        &pio->txf[sm],		// Destination pointer
        output_buf,			// Source pointer
        FRAMES_PER_BUFFER,	// Number of transfers
        true				// Start immediately
    );
    dma_channel_set_irq1_enabled(dma_chan_output, true);
    
#ifndef MULTICORE
	/* No multi-core - just use core 0 */
	
	/* enable IRQ handler for dma input */
    irq_set_exclusive_handler(DMA_IRQ_0, dma_input_handler);
    irq_set_enabled(DMA_IRQ_0, true);

	/* enable IRQ handler for dma output */
    irq_set_exclusive_handler(DMA_IRQ_1, dma_output_handler);
    irq_set_enabled(DMA_IRQ_1, true);
	
	printf("Single core background started\n");
#else
	/* multi-core operation */
	multicore_launch_core1(core1_entry);
	printf("Multicore background started\n");
#endif

	/* Start PIO */
    pio_sm_set_enabled(pio, sm, true);
	printf("PIO started\n");
}

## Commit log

2025-06-07 Create LICENSE
2025-06-09 Update docs, add UDA1345 codec.
2025-06-09 Add a picture

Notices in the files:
codec_pmods/tlv320aic3101_pmod/tlv320aic3101_pmod.kicad_pcb:
(c) 2024
parts and their libraries:
Copyright 2021 Accelerated Designs. All rights reserved.
